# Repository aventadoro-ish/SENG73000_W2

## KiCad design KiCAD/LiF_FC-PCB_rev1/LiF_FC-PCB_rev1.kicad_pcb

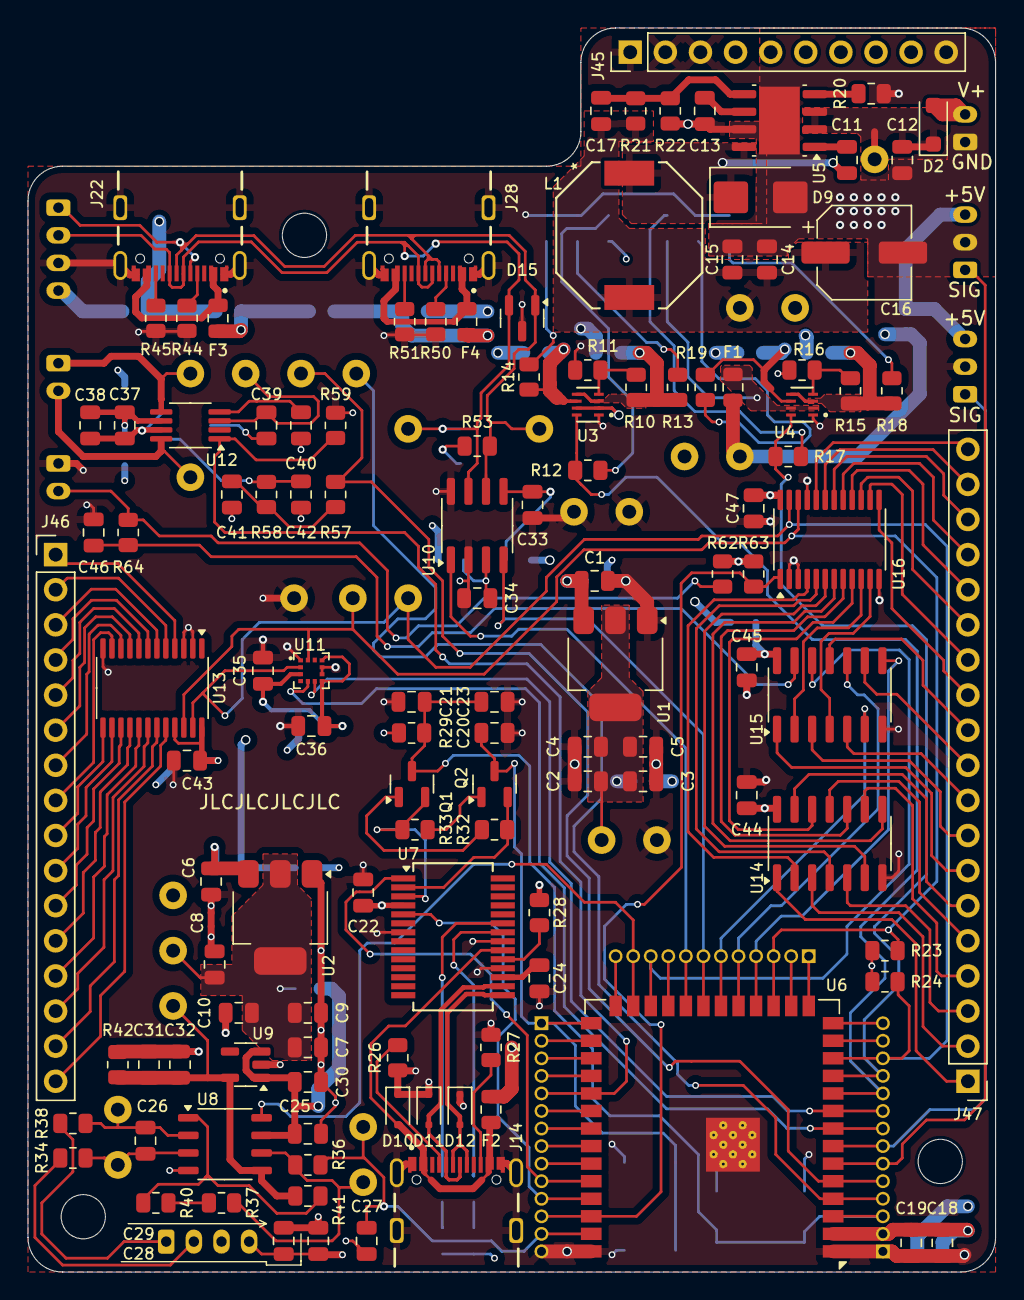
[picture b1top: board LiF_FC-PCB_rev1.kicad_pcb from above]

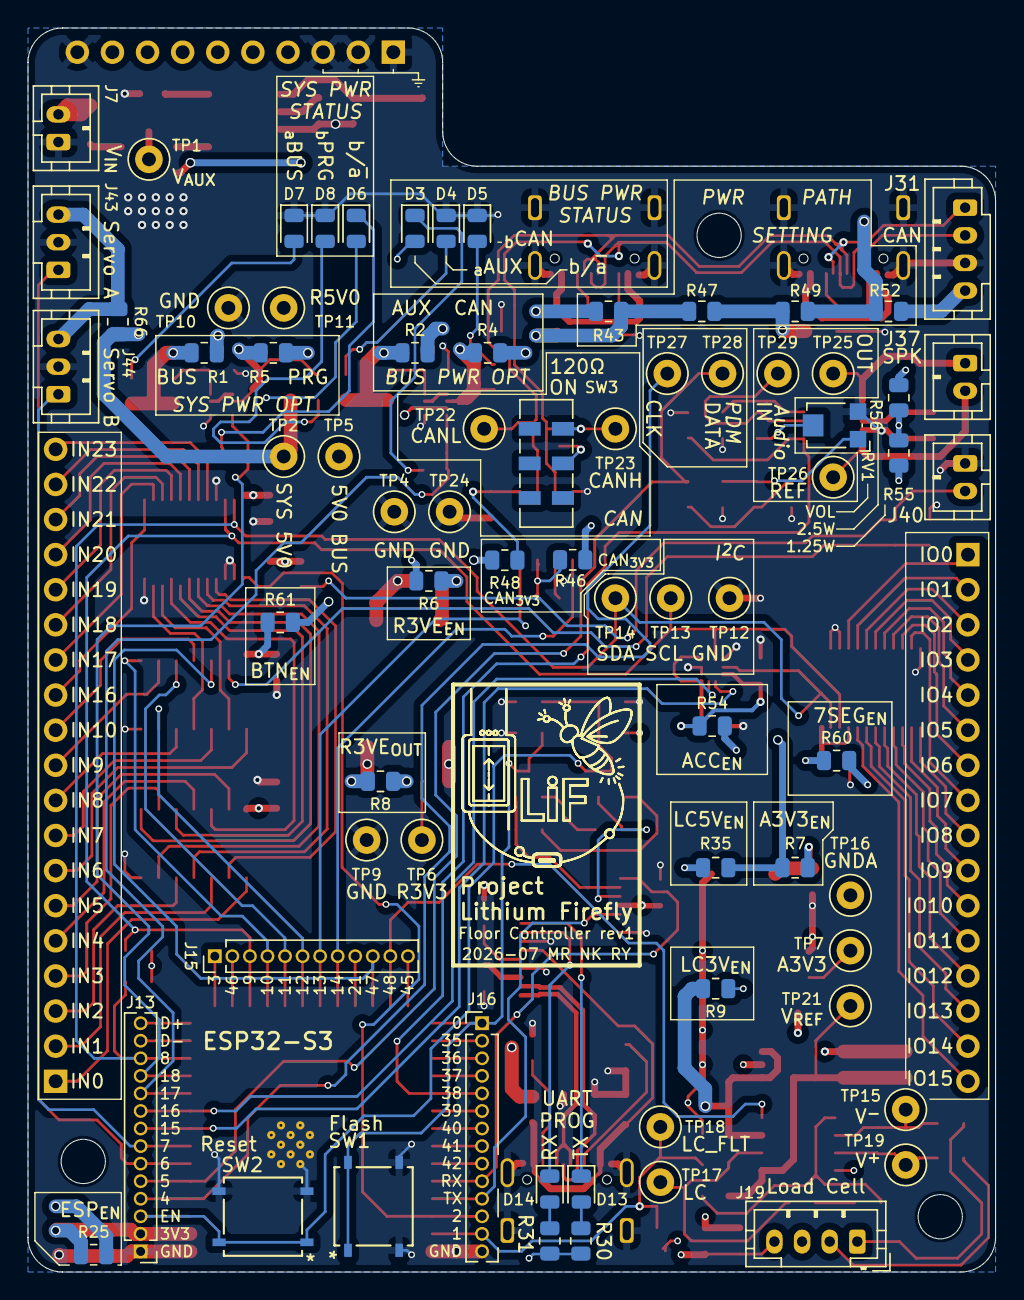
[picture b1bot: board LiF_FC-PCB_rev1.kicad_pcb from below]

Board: 4 copper layers, 70.0 x 90.0 mm, 197 parts (72 on the bottom side), 166 nets.

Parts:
C1, C2, C3, C6, C7, C8, C14, C18, C38: 10u; C_0805_2012Metric
C4, C5, C9, C10, C23, C24, C28, C30, C31, C37, C46: 1u; C_0805_2012Metric
C11, C13, C15, C19, C20, C21, C22, C25, C26, C27, C29, C32, C33, C34, C35, C36, C39, C40, C43, C44, C45, C47: 0.1u; C_0805_2012Metric
C12: 4.7u; C_0805_2012Metric
C16: 270u; CP_Elec_6.3x9.9
C17: 680p; C_0805_2012Metric
C41, C42: 4.7n; C_0805_2012Metric
D2: D; D_SOD-123F
D3, D6: CH2 ON/~{CH1 ON}; LED_0805_2012Metric
D4, D7: CH1; LED_0805_2012Metric
D5, D8: CH2; LED_0805_2012Metric
D9: D; D_SMB
D10, D11, D12: ESD1LIN24DYFR; D_SOD-323F
D13: TX; LED_0805_2012Metric
D14: RX; LED_0805_2012Metric
D15: NUP2105L; SOT-23
F1: 2A; Fuse_0805_2012Metric
F2: 750mA; Fuse_0805_2012Metric
F3, F4: 3A; Fuse_0805_2012Metric
H1, H2, H3: MountingHole; MountingHole_3.2mm_M3_DIN965
J7: V_{IN}; JST_PH_B2B-PH-K_1x02_P2.00mm_Vertical
J13, J16: ESP_DGB_CONN; PinHeader_1x14_P1.27mm_Vertical
J14, J22: CAN Upstream; GCT_USB4105-GF-A
J15: ESP_DGB_CONN; PinHeader_1x12_P1.27mm_Vertical
J19: Load Cell; JST_PH_B4B-PH-K_1x04_P2.00mm_Vertical
J28: CAN Downstream; GCT_USB4105-GF-A
J31: CAN; JST_PH_B4B-PH-K_1x04_P2.00mm_Vertical
J37: SKP OUT; JST_PH_B2B-PH-K_1x02_P2.00mm_Vertical
J40: Door Closed; JST_PH_B2B-PH-K_1x02_P2.00mm_Vertical
J43: Servo A; JST_PH_B3B-PH-K_1x03_P2.00mm_Vertical
J44: Servo B; JST_PH_B3B-PH-K_1x03_P2.00mm_Vertical
J45: Conn_01x10_Socket; PinHeader_1x10_P2.54mm_Vertical
J46: Conn_01x16_Pin; PinHeader_1x16_P2.54mm_Vertical
J47: Conn_01x16_Pin; PinHeader_1x19_P2.54mm_Vertical
L1: 3.8u; IND_BOURNS_SRU1038
NT1: NetTie_2; NetTie-2_SMD_Pad0.5mm
Q1, Q2: MMBT4401; SOT-23
R1, R2, R4, R5, R6, R7, R8, R9, R25, R35, R43, R46, R47, R48, R49, R52, R54, R55, R56, R60, R61, R66: 0; R_0805_2012Metric
R10, R15: 30k; R_0805_2012Metric
R11, R16, R28, R29, R32, R33, R40, R42, R62, R63: 10k; R_0805_2012Metric
R12, R13, R14, R17, R18, R19, R30, R31: 470; R_0805_2012Metric
R20, R59: 73.2k; R_0805_2012Metric
R21: 68k; R_0805_2012Metric
R22: 12k; R_0805_2012Metric
R23, R24: 4.7k; R_0805_2012Metric
R26, R27, R44, R45, R50, R51: 5.1k; R_0805_2012Metric
R34, R38: 47; R_0805_2012Metric
R36: 1k; R_0805_2012Metric
R37: 20k; R_0805_2012Metric
R41, R53: 120; R_0805_2012Metric
R57, R58: 2.2k; R_0805_2012Metric
R64: 100; R_0805_2012Metric
RV1: 10k; Potentiometer_Bourns_TC33X_Vertical
SW1: Flash; SON4_PTS526 SM15 SMTR2 LFS_CNK
SW2: Reset; SON4_PTS526 SM15 SMTR2 LFS_CNK
SW3: CAN Termination; SW_DPDT_CK_JS202011JCQN
TP1: V_{AUX}; TestPoint_Loop_D1.80mm_Drill1.0mm_Beaded
TP2: SYS 5V0; TestPoint_Loop_D1.80mm_Drill1.0mm_Beaded
TP4, TP9, TP10, TP12, TP24: GND; TestPoint_Loop_D1.80mm_Drill1.0mm_Beaded
TP5: 5V0 BUS; TestPoint_Loop_D1.80mm_Drill1.0mm_Beaded
TP6: R3V3; TestPoint_Loop_D1.80mm_Drill1.0mm_Beaded
TP7: A3V3; TestPoint_Loop_D1.80mm_Drill1.0mm_Beaded
TP11: R5V0; TestPoint_Loop_D1.80mm_Drill1.0mm_Beaded
TP13: SCL; TestPoint_Loop_D1.80mm_Drill1.0mm_Beaded
TP14: SDA; TestPoint_Loop_D1.80mm_Drill1.0mm_Beaded
TP15: V^{-}; TestPoint_Loop_D1.80mm_Drill1.0mm_Beaded
TP16: GNDA; TestPoint_Loop_D1.80mm_Drill1.0mm_Beaded
TP17: LC; TestPoint_Loop_D1.80mm_Drill1.0mm_Beaded
TP18: LC_FLT; TestPoint_Loop_D1.80mm_Drill1.0mm_Beaded
TP19: V^{+}; TestPoint_Loop_D1.80mm_Drill1.0mm_Beaded
TP21: V_{REF}; TestPoint_Loop_D1.80mm_Drill1.0mm_Beaded
TP22: CANL; TestPoint_Loop_D1.80mm_Drill1.0mm_Beaded
TP23: CANH; TestPoint_Loop_D1.80mm_Drill1.0mm_Beaded
TP25: Audio_{OUT}; TestPoint_Loop_D1.80mm_Drill1.0mm_Beaded
TP26: Audio_{REF}; TestPoint_Loop_D1.80mm_Drill1.0mm_Beaded
TP27: PDM CLK; TestPoint_Loop_D1.80mm_Drill1.0mm_Beaded
TP28: PDM DATA; TestPoint_Loop_D1.80mm_Drill1.0mm_Beaded
TP29: Audio_{IN}; TestPoint_Loop_D1.80mm_Drill1.0mm_Beaded
U1, U2: AZ1117-3.3; SOT-223-3_TabPin2
U3, U4: TPS2117DRLR; SOT-5x3_DRL0008A_TEX
U5: LMR14050; Texas_R-PDSO-G8_EP2.95x4.9mm_Mask2.4x3.1mm
U6: ESP32-S3-WROOM-1
U7: CY7C65213-28PVXI; SSOP-28_5.3x10.2mm_P0.65mm
U8: MCP6N11-xxxE/SN; JEITA_SOIC-8_3.9x4.9mm_P1.27mm
U9: NCV8114ASN165T1G; TSOT-23-5
U10: MCP2542FD-E/SN; SOIC-8_3.9x4.9mm_P1.27mm
U11: BMA400; XDCR_BMA400
U12: PAM8302AAS; MSOP-8_3x3mm_P0.65mm
U13, U16: NCA9555; TSSOP-24_4.4x7.8mm_P0.65mm
U14, U15: SN74HC14DR; SOIC-14_3.9x8.7mm_P1.27mm

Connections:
/A3V3: C25.1, C30.1, R9.2, U8.7 (VDD), U9.1 (IN), U9.3 (EN)
/Accelerometer/ACC_3V3: C35.1, C36.1, R54.1, U11.3 (VDDIO), U11.7 (VDD), U11.10 (~CSB)
/Accelerometer/ACC_INT1: J13.8, U6.8 (IO15), U11.5 (INT1)
/Accelerometer/ACC_INT2: J13.9, U6.9 (IO16), U11.6 (INT2)
/Accelerometer/I2C.SCL: J15.3, R23.1, TP13.1, U6.17 (IO9), U11.12 (SCX), U13.22 (SCL), U16.22 (SCL)
/Accelerometer/I2C.SDA: J13.12, R24.1, TP14.1, U6.12 (IO8), U11.2 (SDX), U13.23 (SDA), U16.23 (SDA)
/Audio/AMP_{EN}: J16.5, R59.2, U6.31 (IO38), U12.1 (~SD)
/Audio/PDM.CLK: J13.4, TP27.1, U6.4 (IO4)
/Audio/PDM.DATA: J13.5, R57.1, TP28.1, U6.5 (IO5)
/Audio/V_{AMP}: C37.1, C38.1, R55.1, R56.1, U12.6 (VDD)
/Buttons/BTN0: U14.2, U16.4 (IO0_0)
/Buttons/BTN1: U14.4, U16.5 (IO0_1)
/Buttons/BTN2: U14.6, U16.6 (IO0_2)
/Buttons/BTN3: U14.8, U16.7 (IO0_3)
/Buttons/BTN4: U14.10, U16.8 (IO0_4)
/Buttons/BTN5: U14.12, U16.9 (IO0_5)
/Buttons/BTN6: U15.2, U16.10 (IO0_6)
/Buttons/BTN7: U15.4, U16.11 (IO0_7)
/Buttons/BTN_3V3: C44.1, C45.1, C47.1, R61.1, R62.1, R63.1, U14.14 (VCC), U15.14 (VCC), U16.24 (VDD)
/Buttons/DoorLS: J15.10, U6.24 (IO47), U15.12
/Buttons/IN0: J47.1, U14.1
/Buttons/IN1: J47.2, U14.3
/Buttons/IN2: J47.3, U14.5
/Buttons/IN3: J47.4, U14.9
/Buttons/IN4: J47.5, U14.11
/Buttons/IN5: J47.6, U14.13
/Buttons/IN6: J47.7, U15.1
/Buttons/IN7: J47.8, U15.3
/Buttons/IO16: J47.12, U16.13 (IO1_0)
/Buttons/IO17: J47.13, U16.14 (IO1_1)
/Buttons/IO18: J47.14, U16.15 (IO1_2)
/Buttons/IO19: J47.15, U16.16 (IO1_3)
/Buttons/IO20: J47.16, U16.17 (IO1_4)
/Buttons/IO21: J47.17, U16.18 (IO1_5)
/Buttons/IO22: J47.18, U16.19 (IO1_6)
/Buttons/IO23: J47.19, U16.20 (IO1_7)
/Buttons/~BTN_IRQ: J16.12, R63.2, U6.38 (IO2), U16.1 (~INT)
/CAN5V0: D3.2 (A), R1.2, R43.2, TP5.1, U3.2 (V_{OUT}), U3.7 (V_{OUT})
/CAN/CAN5V0_{OUT}: R4.2, R49.1, R52.1
/CAN/CAN+: D15.2 (K), J22.A6 (DP1), J22.B6 (DP2), J28.A6 (DP1), J28.B6 (DP2), J31.2, SW3.6 (C), TP23.1, U10.7 (CANH)
/CAN/CAN-: D15.1 (K), J22.A7 (DN1), J22.B7 (DN2), J28.A7 (DN1), J28.B7 (DN2), J31.1, R53.1, TP22.1, U10.6 (CANL)
/CAN/CAN.RXD: J15.7, U6.21 (IO13), U10.4 (RXD)
/CAN/CAN.TXD: J15.8, U6.22 (IO14), U10.1 (TXD)
/CAN/CAN_3V3: C33.1, R48.1, U10.5 (VIO)
/CAN/CAN_5V0: C34.1, R46.1, U10.3 (VDD)
/CAN/VBUS_DB9: J31.4, R52.2
/CAN/VBUS_Down: F4.2, R43.1, R47.1
/CAN/VBUS_Up: F3.2, R47.2, R49.2
/Display/DISP_3V3: C43.1, R60.1, U13.21 (A0), U13.24 (VDD)
/Display/IO0: J46.1, U13.4 (IO0_0)
/Display/IO1: J46.2, U13.5 (IO0_1)
/Display/IO2: J46.3, U13.6 (IO0_2)
/Display/IO3: J46.4, U13.7 (IO0_3)
/Display/IO4: J46.5, U13.8 (IO0_4)
/Display/IO5: J46.6, U13.9 (IO0_5)
/Display/IO6: J46.7, U13.10 (IO0_6)
/Display/IO7: J46.8, U13.11 (IO0_7)
/Display/IO8: J46.9, U13.13 (IO1_0)
/Display/IO9: J46.10, U13.14 (IO1_1)
/Display/IO10: J46.11, U13.15 (IO1_2)
/Display/IO11: J46.12, U13.16 (IO1_3)
/Display/IO12: J46.13, U13.17 (IO1_4)
/Display/IO13: J46.14, U13.18 (IO1_5)
/Display/IO14: J46.15, U13.19 (IO1_6)
/Display/IO15: J46.16, U13.20 (IO1_7)
/Encoder/ENC.A: J15.4, U6.18 (IO10), U15.8
/Encoder/ENC.B: J15.5, U6.19 (IO11), U15.10
/Encoder/ENC.SW: J15.6, U6.20 (IO12), U15.6
/Encoder/IN8: J47.9, U15.5
/Encoder/IN9: J47.10, U15.9
/Encoder/IN10: J47.11, U15.11
/Load Cell/A+: J19.2, R38.1
/Load Cell/A-: J19.1, R34.2
/Load Cell/E+: C28.1, C29.1, J19.4, R35.1
/Load Cell/Filter V_{OUT}: C27.1, J16.13, R36.1, TP18.1, U6.39 (IO1)
/Load Cell/MCP V_{OUT}: R36.2, R37.2, TP17.1, U8.6 (V_{OUT})
/Load Cell/V_{REF}: C31.1, C32.1, R41.1, R42.2, TP21.1, U8.5 (V_{REF}), U9.5 (OUT)
/MCU/CHIP_PU: C21.1, C23.1, J13.3, Q1.3 (C), R29.1, SW2.1, SW2.2, U6.3 (EN)
/MCU/DTR: Q2.2 (E), R32.1, U7.2 (DTR)
/MCU/ESP32_13: J13.13, U6.13 (USB_D-)
/MCU/ESP32_14: J13.14, U6.14 (USB_D+)
/MCU/ESP32_15: J15.1, U6.15 (IO3)
/MCU/ESP32_16: J15.2, U6.16 (IO46)
/MCU/ESP32_23: J15.9, U6.23 (IO21)
/MCU/ESP32_25: J15.11, U6.25 (IO48), U8.8 (EN/~CAL)
/MCU/ESP32_26: J15.12, U6.26 (IO45)
/MCU/ESP32_27: C20.1, J16.1, Q2.3 (C), SW1.1, SW1.2, U6.27 (IO0)
/MCU/ESP32_28: J16.2, U6.28 (IO35)
/MCU/ESP32_29: J16.3, U6.29 (IO36)
/MCU/ESP32_30: J16.4, U6.30 (IO37)
/MCU/ESP32_32: J16.6, U6.32 (IO39)
/MCU/ESP32_33: J16.7, U6.33 (IO40)
/MCU/ESP32_34: J16.8, U6.34 (IO41)
/MCU/ESP32_35: J16.9, U6.35 (IO42)
/MCU/ESP32_36: J16.10, U6.36 (RXD0), U7.1 (TXD)
/MCU/ESP32_37: J16.11, U6.37 (TXD0), U7.5 (RXD)
/MCU/ESP_3V3: C18.1, C19.1, C22.1, J13.2, R23.2, R24.2, R25.1, R28.2, R29.2, R30.2, R31.2, U6.2 (3V3), U7.4 (VCCIO)
/MCU/RTS: Q1.2 (E), R33.1, U7.3 (RTS)
/MCU/SRV.A: J13.6, J43.1, U6.6 (IO6)
/MCU/SRV.B: J13.7, J44.1, U6.7 (IO7)
/MCU/USB.D+: D12.2 (A2), J14.A6 (DP1), J14.B6 (DP2), U7.15 (USBDP)
/MCU/USB.D-: D11.2 (A2), J14.A7 (DN1), J14.B7 (DN2), U7.16 (USBDM)
/MCU/USB_VBUS: D10.2 (A2), F2.1, J14.A4_B9 (VBUS), J14.B4_A9 (VBUS__1), U7.20 (VCC)
/MCU/V_{PROG USB}: F2.2, R5.2
/MCU/V_{ST}.AUX: J13.10, R12.2, U3.8 (ST), U6.10 (IO17)
/MCU/V_{ST}.SYS: J13.11, R17.2, U4.8 (ST), U6.11 (IO18)
/Power Regulation/5V Regulator/Boot: C11.1, U5.1 (BOOT)
/Power Regulation/5V Regulator/REG5V_in: C12.1, D2.1 (K), TP1.1, U5.2 (VIN), U5.3 (EN)
/Power Regulation/5V Regulator/REG5V_out: C14.1, C15.1, C16.1, C17.1, L1.2, R2.2, R21.1, TP11.1
/Power Regulation/5V Regulator/SW: C11.2, D9.1 (K), L1.1, U5.8 (SW)
/Power Regulation/A3V3_out: C7.1, C8.1, C9.1, C10.1, R9.1, TP7.1, U2.2 (VO)
/Power Regulation/Power OR-ing1/V_{IN1}: R1.1, R15.1, R18.2, U4.3 (V_{IN1}), U4.5 (MODE)
/Power Regulation/Power OR-ing1/V_{IN2}: R5.1, R19.2, U4.6 (V_{IN2})
/Power Regulation/Power OR-ing1/V_{out}: D6.2 (A), F1.1, U4.2 (V_{OUT}), U4.7 (V_{OUT})
/Power Regulation/Power OR-ing1/V_{threshold}: R15.2, R16.1, U4.4 (PR1)
/Power Regulation/Power OR-ing/V_{IN1}: R2.1, R10.1, R13.2, U3.3 (V_{IN1}), U3.5 (MODE)
/Power Regulation/Power OR-ing/V_{IN2}: R4.1, R14.2, U3.6 (V_{IN2})
/Power Regulation/Power OR-ing/V_{threshold}: R10.2, R11.1, U3.4 (PR1)
/Power Regulation/R3V3_out: C2.1, C3.1, C4.1, C5.1, R8.1, TP6.1, U1.2 (VO)
/R3V3: J45.4, J45.5, R8.2, R25.2, R48.2, R54.2, R55.2, R60.2, R61.2
/SYS5V0: F1.2, J45.6, J45.7, R6.2, R7.2, R35.2, R46.2, R56.2, R66.2, TP2.1
/Servos/SRV_5V0: J43.3, J44.3, R66.1
/Stackup Header/V_{supply}: D2.2 (A), J7.2, J45.8, J45.9
GND: C1.2, C2.2, C3.2, C4.2, C5.2, C6.2, C12.2, C13.2, C14.2, C15.2, C16.2, C18.2, C19.2, C20.2, C21.2, C22.2, C23.2, C24.2, C33.2, C34.2, C35.2, C36.2, C37.2, C38.2, C40.1, C41.2, C42.2, C43.2, C44.2, C45.2, C46.2, C47.2, D4.1 (K), D5.1 (K), D7.1 (K), D8.1 (K), D9.2 (A), D10.1 (A1), D11.1 (A1), D12.1 (A1), D15.3 (A), J7.1, J13.1, J14.A1_B12 (GND), J14.B1_A12 (GND__1), J14.SH1 (SHELL_GND), J14.SH2 (SHELL_GND__1), J14.SH3 (SHELL_GND__2), J14.SH4 (SHELL_GND__3), J16.14, J22.A1_B12 (GND), J22.B1_A12 (GND__1), J22.SH1 (SHELL_GND), J22.SH2 (SHELL_GND__1), J22.SH3 (SHELL_GND__2), J22.SH4 (SHELL_GND__3), J28.A1_B12 (GND), J28.B1_A12 (GND__1), J28.SH1 (SHELL_GND), J28.SH2 (SHELL_GND__1), J28.SH3 (SHELL_GND__2), J28.SH4 (SHELL_GND__3), J31.3, J40.1, J43.2, J44.2, J45.1, J45.2, J45.3, J45.10, NT1.1, R11.2, R16.2, R20.2, R22.2, R26.1, R27.1, R44.1, R45.1, R50.1, R51.1, R59.1, RV1.3, SW1.3, SW1.4, SW2.3, SW2.4, TP4.1, TP9.1, TP10.1, TP12.1, TP24.1, U1.1 (GND), U3.1 (GND), U4.1 (GND), U5.7 (GND), U5.9 (PGND), U6.1 (GND), U6.40 (GND), U6.41 (GND), U7.7 (GND), U7.18 (GND), U7.21 (GND), U10.2 (VSS), U10.8 (STBY), U11.1 (SDO), U11.8 (GNDIO), U11.9 (GND), U12.7 (GND), U13.2 (A1), U13.3 (A2), U13.12 (VSS), U14.7 (GND), U15.7 (GND), U16.2 (A1), U16.3 (A2), U16.12 (VSS), U16.21 (A0)
GNDA: C7.2, C8.2, C9.2, C10.2, C25.2, C27.2, C28.2, C29.2, C30.2, C31.2, C32.2, J19.3, NT1.2, R42.1, TP16.1, U2.1 (GND), U8.4 (VSS), U9.2 (GND)
unnamed: C39.1, RV1.2
unnamed: C41.1, R57.2, R58.1
unnamed: C42.1, R58.2, RV1.1
unnamed: C46.1, R64.2, U15.13
unnamed: D3.1 (K), R12.1
unnamed: D4.2 (A), R13.1
unnamed: D5.2 (A), R14.1
unnamed: D6.1 (K), R17.1
unnamed: D7.2 (A), R18.1
unnamed: D8.2 (A), R19.1
unnamed: D13.2 (A), R30.1
unnamed: D13.1 (K), U7.23 (GPIO0)
unnamed: D14.2 (A), R31.1
unnamed: D14.1 (K), U7.22 (GPIO1)
unnamed: J14.A5 (CC1), R26.2
unnamed: J14.B5 (CC2), R27.2
unnamed: J22.A5 (CC1), R44.2
unnamed: J22.B5 (CC2), R45.2
unnamed: F3.1, J22.A4_B9 (VBUS), J22.B4_A9 (VBUS__1)
unnamed: J28.A5 (CC1), R50.2
unnamed: J28.B5 (CC2), R51.2
unnamed: F4.1, J28.A4_B9 (VBUS), J28.B4_A9 (VBUS__1)
unnamed: J37.1, TP25.1, U12.5 (OUT+)
unnamed: J37.2, TP26.1, U12.8 (OUT-)
unnamed: J40.2, R62.2, R64.1
unnamed: Q1.1 (B), R32.2
unnamed: Q2.1 (B), R33.2
unnamed: R37.1, R40.2
unnamed: R53.2, SW3.5 (B)
unnamed: C1.1, R6.1, U1.3 (VI)
unnamed: C6.1, R7.1, U2.3 (VI)
unnamed: C17.2, R21.2, R22.1, U5.5 (FB)
unnamed: R20.1, U5.4 (RT/SYNC)
unnamed: C13.1, U5.6 (SS)
unnamed: C24.1, U7.17 (VCCD)
unnamed: R28.1, U7.19 (~RESET)
unnamed: C26.2, R38.2, TP19.1, U8.3 (V^{+})
unnamed: C26.1, R34.1, TP15.1, U8.2 (V^{-})
unnamed: R40.1, R41.2, U8.1 (V_{FG})
unnamed: C39.2, TP29.1, U12.3 (IN+)
unnamed: C40.2, U12.4 (IN-)

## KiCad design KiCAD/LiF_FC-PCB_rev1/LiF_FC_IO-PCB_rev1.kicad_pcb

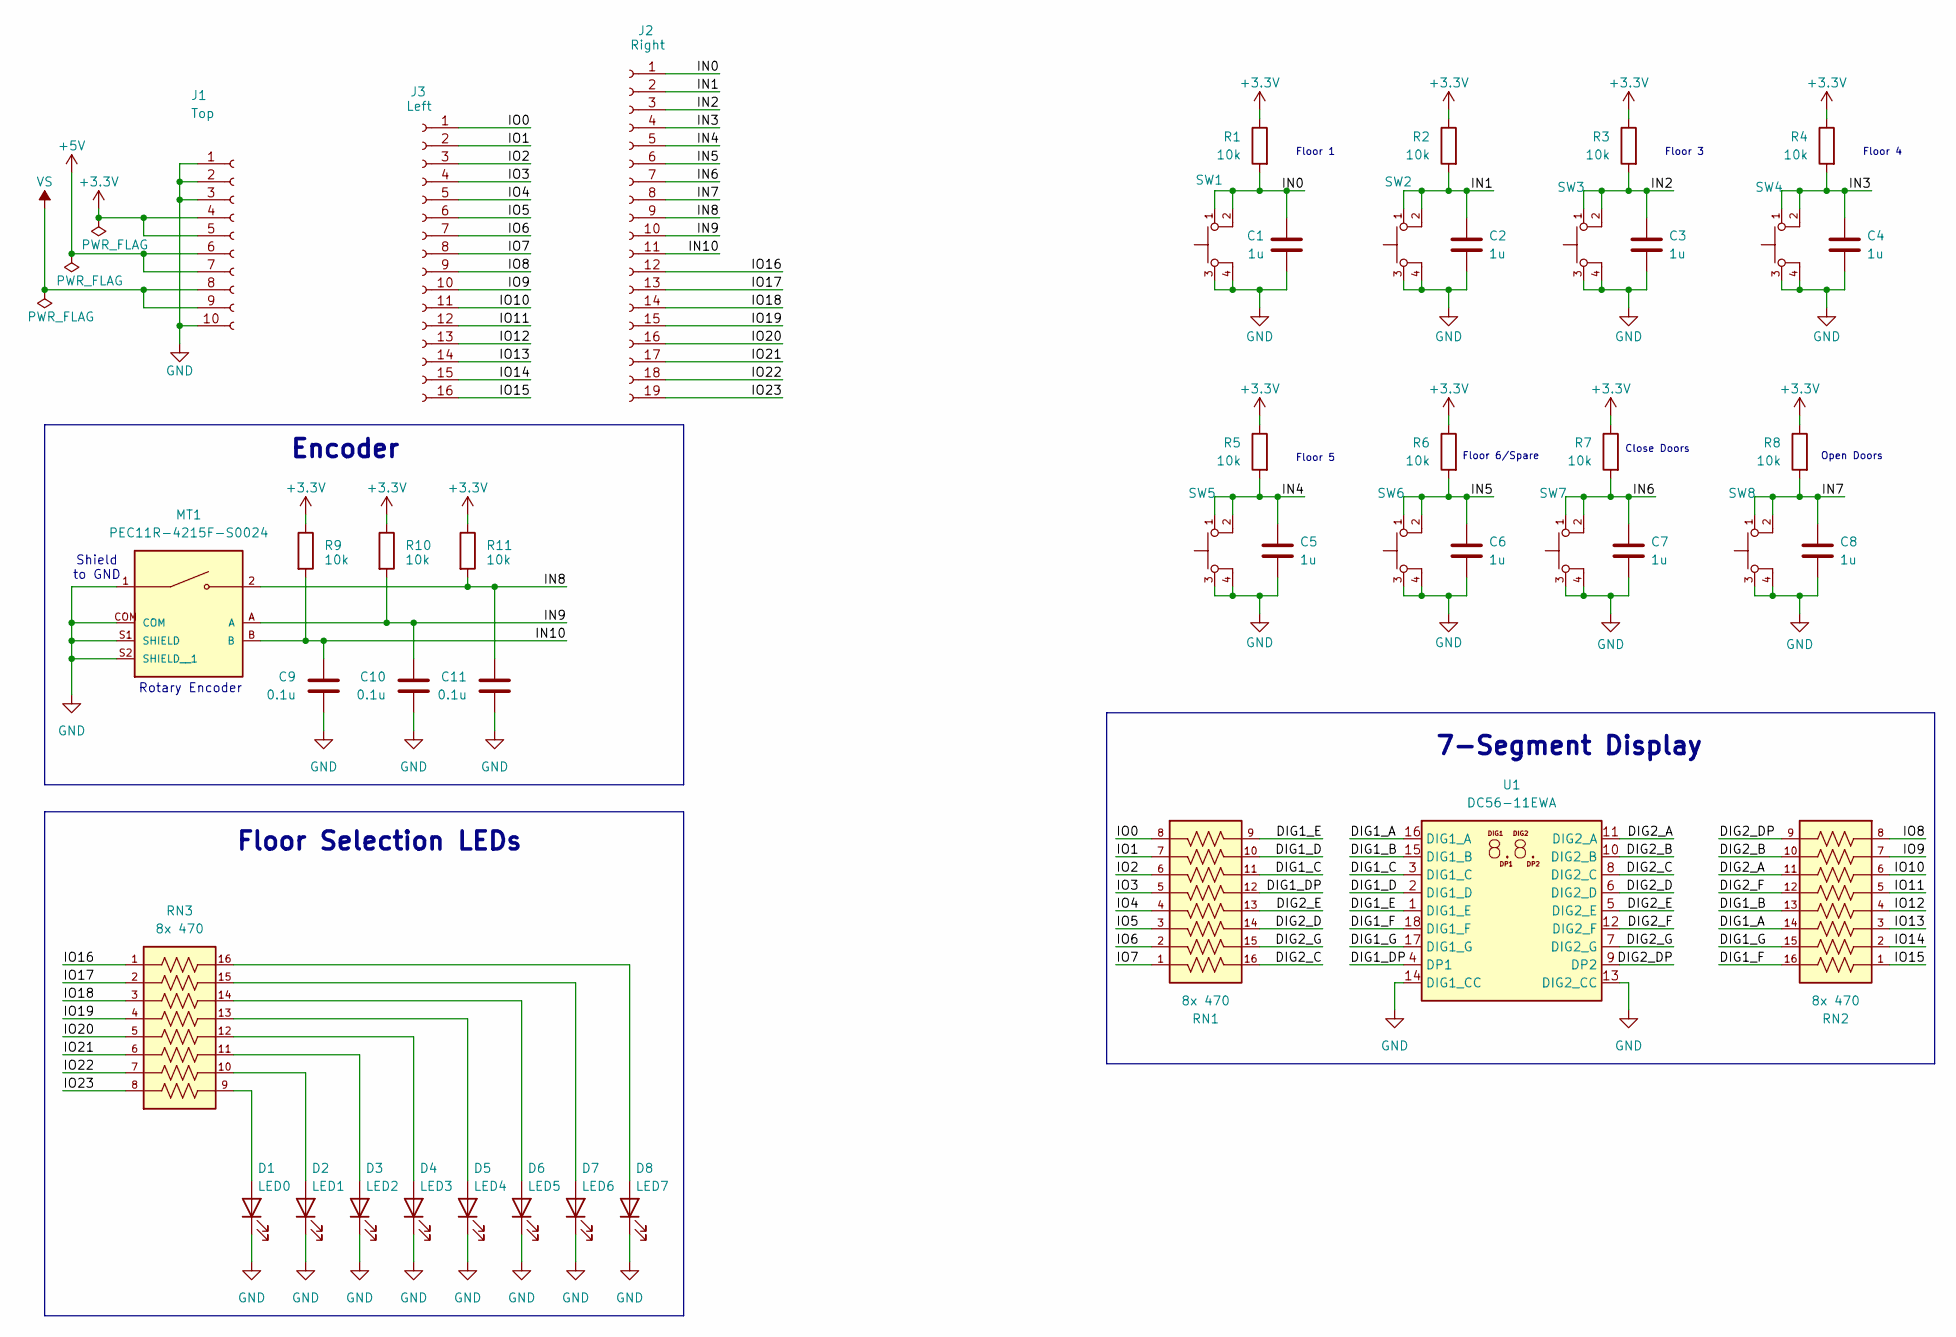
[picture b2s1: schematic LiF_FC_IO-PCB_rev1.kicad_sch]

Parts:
C1, C2, C3, C4, C5, C6, C7, C8: 1u; C_0805_2012Metric
C9, C10, C11: 0.1u; C_0805_2012Metric
D1: LED0; LED_0805_2012Metric
D2: LED1; LED_0805_2012Metric
D3: LED2; LED_0805_2012Metric
D4: LED3; LED_0805_2012Metric
D5: LED4; LED_0805_2012Metric
D6: LED5; LED_0805_2012Metric
D7: LED6; LED_0805_2012Metric
D8: LED7; LED_0805_2012Metric
J1: Top; PinSocket_1x10_P2.54mm_Vertical
J2: Right; PinSocket_1x19_P2.54mm_Vertical
J3: Left; PinSocket_1x16_P2.54mm_Vertical
MT1: PEC11R-4215F-S0024; XDCR_PEC11R-4215F-S0024; PARTREV Rev. 09/19
R1, R2, R3, R4, R5, R6, R7, R8, R9, R10, R11: 10k; R_0805_2012Metric
RN1, RN2, RN3: 8x 470; RESCAXE50P380X160X55-16N; PARTREV 1-Mar-20
SW1, SW2, SW3, SW4, SW5, SW6, SW7, SW8: TL3301PF160QG; SW_TL3301PF160QG; PARTREV E
U1: DC56-11EWA; DA56-11SURKWA

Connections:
+3.3V: J1.4, J1.5, R1.1, R2.1, R3.1, R4.1, R5.1, R6.1, R7.1, R8.1, R9.1, R10.1, R11.1
+5V: J1.6, J1.7
/DIG1_A: RN2.14, U1.16 (DIG1_A)
/DIG1_B: RN2.13, U1.15 (DIG1_B)
/DIG1_C: RN1.11, U1.3 (DIG1_C)
/DIG1_D: RN1.10, U1.2 (DIG1_D)
/DIG1_DP: RN1.12, U1.4 (DP1)
/DIG1_E: RN1.9, U1.1 (DIG1_E)
/DIG1_F: RN2.16, U1.18 (DIG1_F)
/DIG1_G: RN2.15, U1.17 (DIG1_G)
/DIG2_A: RN2.11, U1.11 (DIG2_A)
/DIG2_B: RN2.10, U1.10 (DIG2_B)
/DIG2_C: RN1.16, U1.8 (DIG2_C)
/DIG2_D: RN1.14, U1.6 (DIG2_D)
/DIG2_DP: RN2.9, U1.9 (DP2)
/DIG2_E: RN1.13, U1.5 (DIG2_E)
/DIG2_F: RN2.12, U1.12 (DIG2_F)
/DIG2_G: RN1.15, U1.7 (DIG2_G)
/IN0: C1.1, J2.1, R1.2, SW1.1, SW1.2
/IN1: C2.1, J2.2, R2.2, SW2.1, SW2.2
/IN2: C3.1, J2.3, R3.2, SW3.1, SW3.2
/IN3: C4.1, J2.4, R4.2, SW4.1, SW4.2
/IN4: C5.1, J2.5, R5.2, SW5.1, SW5.2
/IN5: C6.1, J2.6, R6.2, SW6.1, SW6.2
/IN6: C7.1, J2.7, R7.2, SW7.1, SW7.2
/IN7: C8.1, J2.8, R8.2, SW8.1, SW8.2
/IN8: C11.1, J2.9, MT1.2, R11.2
/IN9: C10.1, J2.10, MT1.A, R10.2
/IN10: C9.1, J2.11, MT1.B, R9.2
/IO0: J3.1, RN1.8
/IO1: J3.2, RN1.7
/IO2: J3.3, RN1.6
/IO3: J3.4, RN1.5
/IO4: J3.5, RN1.4
/IO5: J3.6, RN1.3
/IO6: J3.7, RN1.2
/IO7: J3.8, RN1.1
/IO8: J3.9, RN2.8
/IO9: J3.10, RN2.7
/IO10: J3.11, RN2.6
/IO11: J3.12, RN2.5
/IO12: J3.13, RN2.4
/IO13: J3.14, RN2.3
/IO14: J3.15, RN2.2
/IO15: J3.16, RN2.1
/IO16: J2.12, RN3.1
/IO17: J2.13, RN3.2
/IO18: J2.14, RN3.3
/IO19: J2.15, RN3.4
/IO20: J2.16, RN3.5
/IO21: J2.17, RN3.6
/IO22: J2.18, RN3.7
/IO23: J2.19, RN3.8
GND: C1.2, C2.2, C3.2, C4.2, C5.2, C6.2, C7.2, C8.2, C9.2, C10.2, C11.2, D1.1 (K), D2.1 (K), D3.1 (K), D4.1 (K), D5.1 (K), D6.1 (K), D7.1 (K), D8.1 (K), J1.1, J1.2, J1.3, J1.10, MT1.1, MT1.COM, MT1.S1 (SHIELD), MT1.S2 (SHIELD__1), SW1.3, SW1.4, SW2.3, SW2.4, SW3.3, SW3.4, SW4.3, SW4.4, SW5.3, SW5.4, SW6.3, SW6.4, SW7.3, SW7.4, SW8.3, SW8.4, U1.13 (DIG2_CC), U1.14 (DIG1_CC)
unnamed: D1.2 (A), RN3.9
unnamed: D2.2 (A), RN3.10
unnamed: D3.2 (A), RN3.11
unnamed: D4.2 (A), RN3.12
unnamed: D5.2 (A), RN3.13
unnamed: D6.2 (A), RN3.14
unnamed: D7.2 (A), RN3.15
unnamed: D8.2 (A), RN3.16
VS: J1.8, J1.9

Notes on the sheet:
Rotary Encoder
Floor 1
Floor Selection LEDs
Floor 3
Open Doors
Floor 4
Encoder
7-Segment Display
Floor 5
Close Doors
Floor 6/Spare
Shield to GND

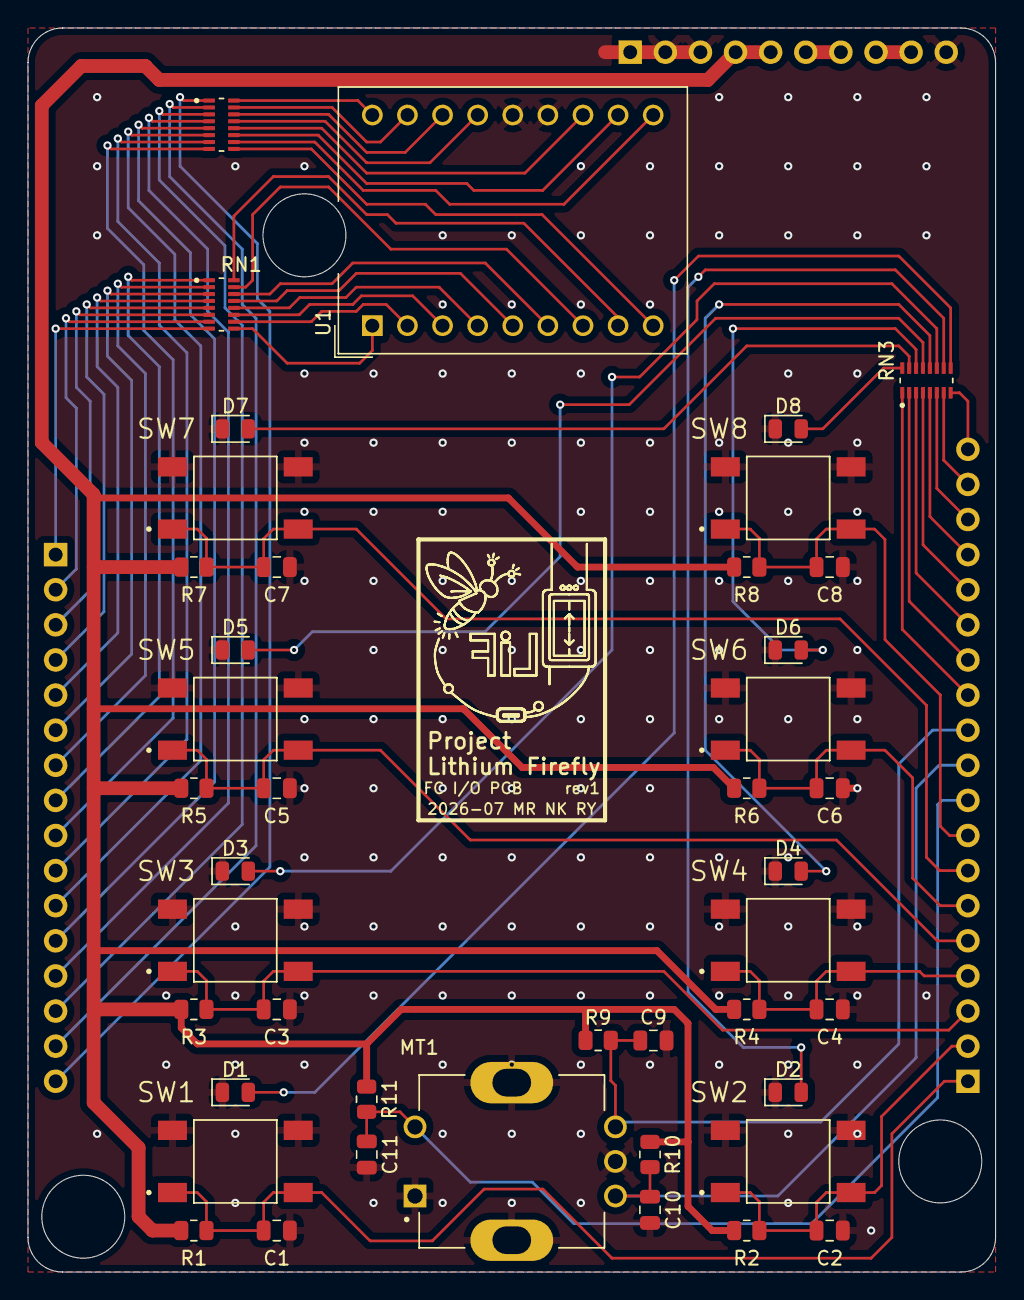
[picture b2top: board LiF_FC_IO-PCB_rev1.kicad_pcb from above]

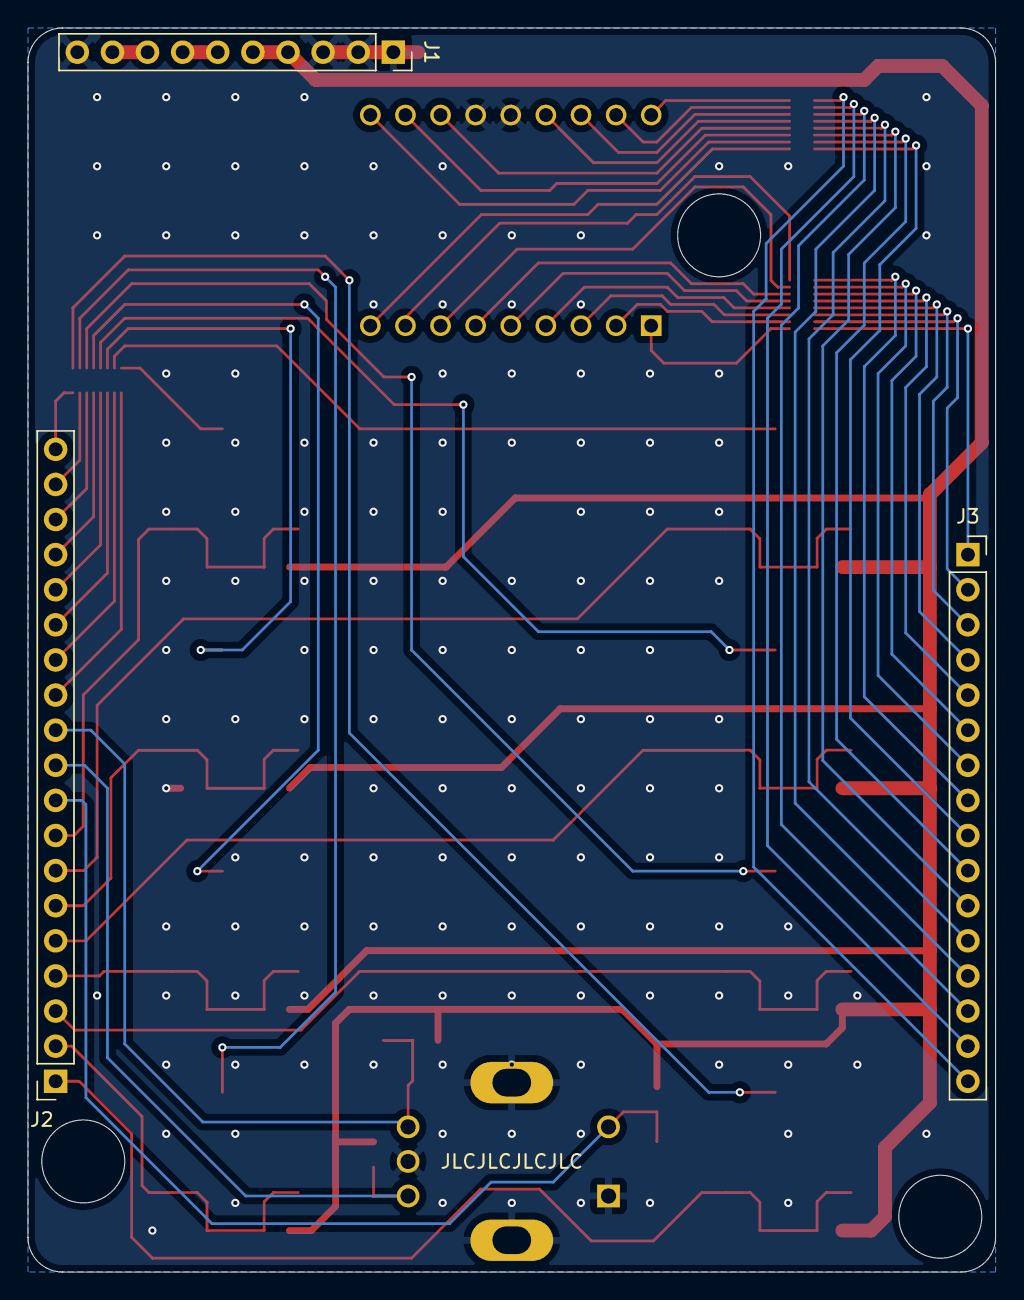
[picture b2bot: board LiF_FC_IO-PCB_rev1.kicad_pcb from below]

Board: 2 copper layers, 70.0 x 90.0 mm, 46 parts (3 on the bottom side), 63 nets.

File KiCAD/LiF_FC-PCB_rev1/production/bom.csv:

Designator,Footprint,Quantity,Value,LCSC Part #
"C1, C2, C3, C4, C5, C6, C7, C8",0805,8,1u,
"C10, C11, C9",0805,3,0.1u,
D1,0805,1,LED0,
D2,0805,1,LED1,
D3,0805,1,LED2,
D4,0805,1,LED3,
D5,0805,1,LED4,
D6,0805,1,LED5,
D7,0805,1,LED6,
D8,0805,1,LED7,
J1,PinSocket_1x10_P2.54mm_Vertical,1,Top,
J2,PinSocket_1x19_P2.54mm_Vertical,1,Right,
J3,PinSocket_1x16_P2.54mm_Vertical,1,Left,
MT1,XDCR_PEC11R-4215F-S0024,1,PEC11R-4215F-S0024,
"R1, R10, R11, R2, R3, R4, R5, R6, R7, R8, R9",0805,11,10k,
"RN1, RN2, RN3",RESCAXE50P380X160X55-16N,3,8x 470,
"SW1, SW2, SW3, SW4, SW5, SW6, SW7, SW8",SW_TL3301PF160QG,8,TL3301PF160QG,
U1,DA56-11SURKWA,1,DC56-11EWA,

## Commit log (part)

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2026-05-22 initial commit. added readme
2026-05-22 added some webpages
2026-05-22 refininf basic pages during lecture
2026-05-22 added form prototype
2026-05-22 slightly improved security of the login form
2026-05-25 added login page and started logbook template
2026-05-27 created personal logbook cover page template and used it to populate my logbook page
2026-05-27 implemented logbook entry template
2026-05-27 fixed typos and added a logbook entry
2026-05-27 fixed broken links in logbook cover template and personal logbook cover
2026-05-27 updated logbook entry template to include a link to each person's cover page
2026-05-27 small update to logbook templates
2026-05-27 added a backlogged entry and fixed minor template issues
2026-06-01 added draft CAD model logbook entry
2026-06-01 added icon and logbook entries
2026-06-01 added navbar
2026-06-01 Updated logbook for week 3 from the template
2026-06-01 STM32 CubeIDE and CubeMX initialized
2026-06-01 fixing STM32 CubeIDE version
2026-06-01 reconfigured STM32 project for an older CubeIDE version. Tested compilation and upload with a blinking LED
2026-06-01 added feature
2026-06-02 Restructured RY logbook (added a coverpage and moved the entry in that cover page to the entries_RY page
2026-06-05 Updating my Logbook - NK
2026-06-06 Added Rita's portrait
2026-06-06 Week 4 group photo with the start of the hardware
2026-06-06 saving current changes before pull for week 4
2026-06-06 added my logbook entries, add pictures from the week, filled in the Gantt chart
2026-06-06 more modifications from Week 1-4 for Rita
2026-06-06 added reference documents
2026-06-07 Rename portrait_RY.jpg to portrait_RYnope.jpg
    Don't use this one
2026-06-07 Use this portrait_RY.jpg
2026-06-07 fixed typo
2026-06-07 Project Details Fig. 1 and 2
2026-06-07 Fixing June 5 image pathway and to cover page
2026-06-07 updated STM32 Code and my own logbook
2026-06-07 minor css path fix
2026-06-07 Project Charter 2026
2026-06-08 Tested CAN communication and wrote logbook entry. This commit only has the logbook, code and IOC changes are omitted not to break main configuration
2026-06-14 initial stepper implementation that works
2026-06-14 implemented a more advanced serial interface to control the motor
2026-06-14 added sweep feature to the stepper software
2026-06-14 Logbook and RPi4 C++ code from week 5
2026-06-14 improved CAN transmit, implemented CAN receive; added fast flashing for STMs via #ifdefs; wrote PB and LED logic; updated logbook
2026-06-14 added logbook entries and accidentally added Arduino code for EC
2026-06-14 Stepper motor working with STM32
2026-06-14 removing unncessary .pio build files
2026-06-14 Adding CAN bus support
2026-06-14 started organizing code into modules and namespaces
2026-06-14 modified stepepr module - needs testing. fixed CAN module compilation errors
2026-06-15 tested generated motor control code. seems to work ok, but movemm command results in rejected
2026-06-15 testing motor code, movemm works, but travel is limited strangely - need to look into that
2026-06-15 refactor motor serial test code
2026-06-17 stopped tracking Debug STM files, minor changes to EC code
2026-06-17 Fully implemented EC. Needs testing
2026-06-17 added logbook entries, PHP, RPi4 code and map to the About page
2026-06-17 added comments
2026-06-17 moved folders to appropriate locations, added .vscode to .gitignore
2026-06-17 Reorganized php and RPi folders and cleaned logbook entries
2026-06-18 logbooks + bugfixed in EC code
2026-06-18 FSM push 1
2026-06-18 added project plan, login pages, updated Gantt Chart
2026-06-18 small bugfix
2026-06-18 Updated logo about page
2026-06-18 fixed merge errors
2026-06-19 updated STM32 LED logic (non-blocking), add toggle switch functionality, updated my logbook, created .css file for code formatting (prism.js), and piyushed
2026-06-19 modified project details css
2026-06-19 updated logbook
2026-06-19 Ignore CubeIDE language settings - merge conflicts every damn time
2026-06-19 Ignore CubeIDE language settings globally
2026-06-19 RPi Demo 1
2026-06-19 adding logbook entries, work in progress
2026-06-19 About page is fully done
2026-06-19 Added a plaecholder for the video team intro
2026-06-19 added team introduction video
2026-06-19 made sure all pages have meta tags
2026-06-19 added HTML5 compatability directive to all webpages
2026-06-19 added CSS rule for HTML5 compatibility
2026-06-19 made sure all pages have copyright
2026-06-19 added master.css link to all pages
2026-06-19 Added required links to project plan as per SENG73000 assignment 1
2026-06-19 updated Gantt Chart
2026-06-19 PHP files for Login and Request Access HTML
2026-06-19 php and login page
2026-06-19 website changes and CC/FC changes.
2026-06-19 modified the php files
2026-06-19 added the php 2.0
2026-06-19 fixed css path in login
2026-06-19 patched index.html merge conflict
2026-06-19 fixed formatting issue with aside in proj_details
2026-06-19 fixed red tex in proj_detail.css
2026-06-19 added if statement for the submitted
2026-06-20 fixed php logic
2026-06-20 some work on A1
2026-06-20 more code added
2026-06-20 new JS logic, few new HTML files for navbar
2026-06-20 Added bootstrap and mystyle.css
2026-06-20 deleted accidentelly kept file
2026-06-20 added a tropical style to mystyle.css and changed the home page
2026-06-20 quick-fix for Q21 of SENG A1
2026-06-21 updated master.css slightly, will continue to update over the next two hours... Let me COOK
2026-06-21 copied RPi code to LiF_SC
2026-06-21 restored makefile to original, as new version was added by mistake
2026-06-21 modified makefile to account for new LiF_SC structure
2026-06-21 setup a workflow to quickly upload LiF_SC to RPi using VSCode Build Task
2026-06-21 added a guide for team members to deploy code to RPi
2026-06-21 modified build task to also run make clean and make on RPi after transferring files
2026-06-21 changed makefile for rpi for executable file to have a proper name
2026-06-21 fixed STM Debug folder tracking and added door switch functionality to SC FSM
2026-06-21 fixing logic of CC and SC for everything to work together
2026-06-21 configured floor steps and fixed print statements
2026-06-22 Added logbooks for week 6
2026-06-22 big website update! The big leagues are calling.
2026-06-22 added print statements to FC and CC
2026-06-22 continued to update the website
2026-06-22 Added logic to the FSM
2026-06-22 revamped rita's logbook and worked on formatting my own
2026-06-23 patched CAN table
